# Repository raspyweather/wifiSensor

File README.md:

# wifiSensor

A project using two Wemos D1 minis, used to measure the Wifi connectivity between each other.
By using a cheap 3.7V Lithium battery, an 8x8 LED matrix shield and an additional PCB for having a more compact design.

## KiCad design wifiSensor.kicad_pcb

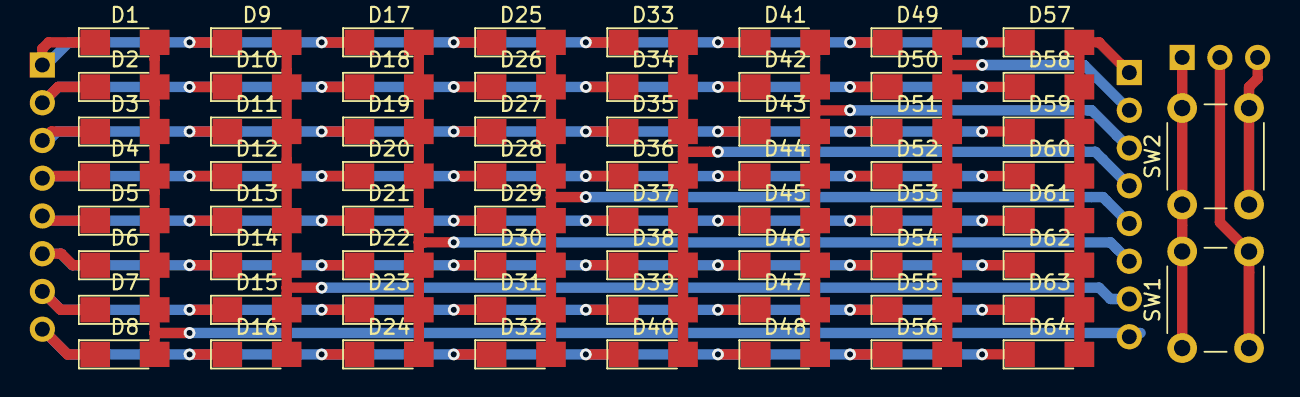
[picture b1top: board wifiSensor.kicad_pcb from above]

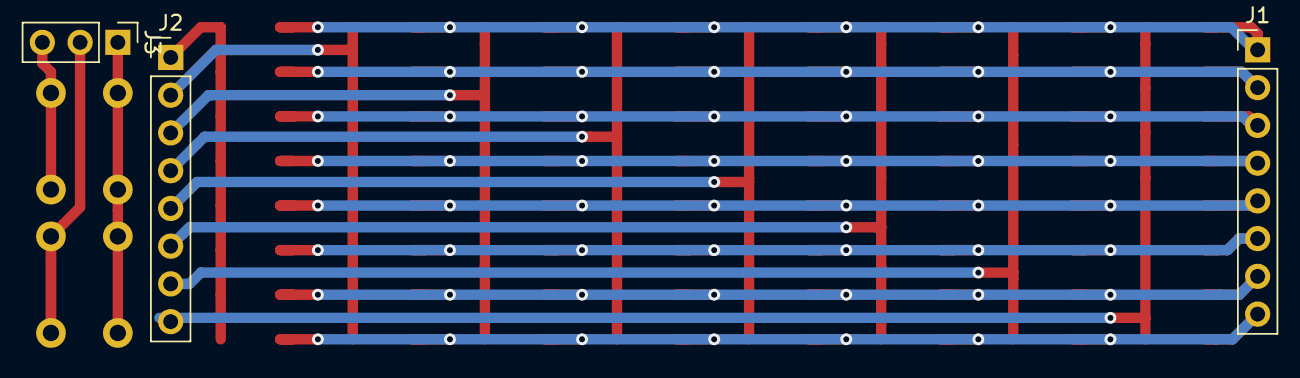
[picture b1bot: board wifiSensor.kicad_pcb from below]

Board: 2 copper layers, 69 parts (3 on the bottom side), 19 nets.

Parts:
D1, D2, D3, D4, D5, D6, D7, D8, D9, D10, D11, D12, D13, D14, D15, D16, D17, D18, D19, D20, D21, D22, D23, D24, D25, D26, D27, D28, D29, D30, D31, D32, D33, D34, D35, D36, D37, D38, D39, D40, D41, D42, D43, D44, D45, D46, D47, D48, D49, D50, D51, D52, D53, D54, D55, D56, D57, D58, D59, D60, D61, D62, D63, D64: LED; LED_1206_HandSoldering
J1, J2: Conn_01x08; Pin_Header_Straight_1x08_Pitch2.54mm
J3: Conn_01x03; Pin_Header_Straight_1x03_Pitch2.54mm
SW1, SW2: SW_Push; SW_PUSH_6mm

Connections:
unnamed: D1.1, D9.1, D17.1, D25.1, D33.1, D41.1, D49.1, D57.1, J1.1
unnamed: D1.2, D2.2, D3.2, D4.2, D5.2, D6.2, D7.2, D8.2, J2.8
unnamed: D2.1, D10.1, D18.1, D26.1, D34.1, D42.1, D50.1, D58.1, J1.2
unnamed: D9.2, D10.2, D11.2, D12.2, D13.2, D14.2, D15.2, D16.2, J2.7
unnamed: D3.1, D11.1, D19.1, D27.1, D35.1, D43.1, D51.1, D59.1, J1.3
unnamed: D4.1, D12.1, D20.1, D28.1, D36.1, D44.1, D52.1, D60.1, J1.4
unnamed: D5.1, D13.1, D21.1, D29.1, D37.1, D45.1, D53.1, D61.1, J1.5
unnamed: D6.1, D14.1, D22.1, D30.1, D38.1, D46.1, D54.1, D62.1, J1.6
unnamed: D7.1, D15.1, D23.1, D31.1, D39.1, D47.1, D55.1, D63.1, J1.7
unnamed: D8.1, D16.1, D24.1, D32.1, D40.1, D48.1, D56.1, D64.1, J1.8
unnamed: D17.2, D18.2, D19.2, D20.2, D21.2, D22.2, D23.2, D24.2, J2.6
unnamed: D25.2, D26.2, D27.2, D28.2, D29.2, D30.2, D31.2, D32.2, J2.5
unnamed: D33.2, D34.2, D35.2, D36.2, D37.2, D38.2, D39.2, D40.2, J2.4
unnamed: D41.2, D42.2, D43.2, D44.2, D45.2, D46.2, D47.2, D48.2, J2.3
unnamed: D49.2, D50.2, D51.2, D52.2, D53.2, D54.2, D55.2, D56.2, J2.2
unnamed: D57.2, D58.2, D59.2, D60.2, D61.2, D62.2, D63.2, D64.2, J2.1
unnamed: J3.1, SW1.1, SW2.1
unnamed: J3.2, SW1.2
unnamed: J3.3, SW2.2
